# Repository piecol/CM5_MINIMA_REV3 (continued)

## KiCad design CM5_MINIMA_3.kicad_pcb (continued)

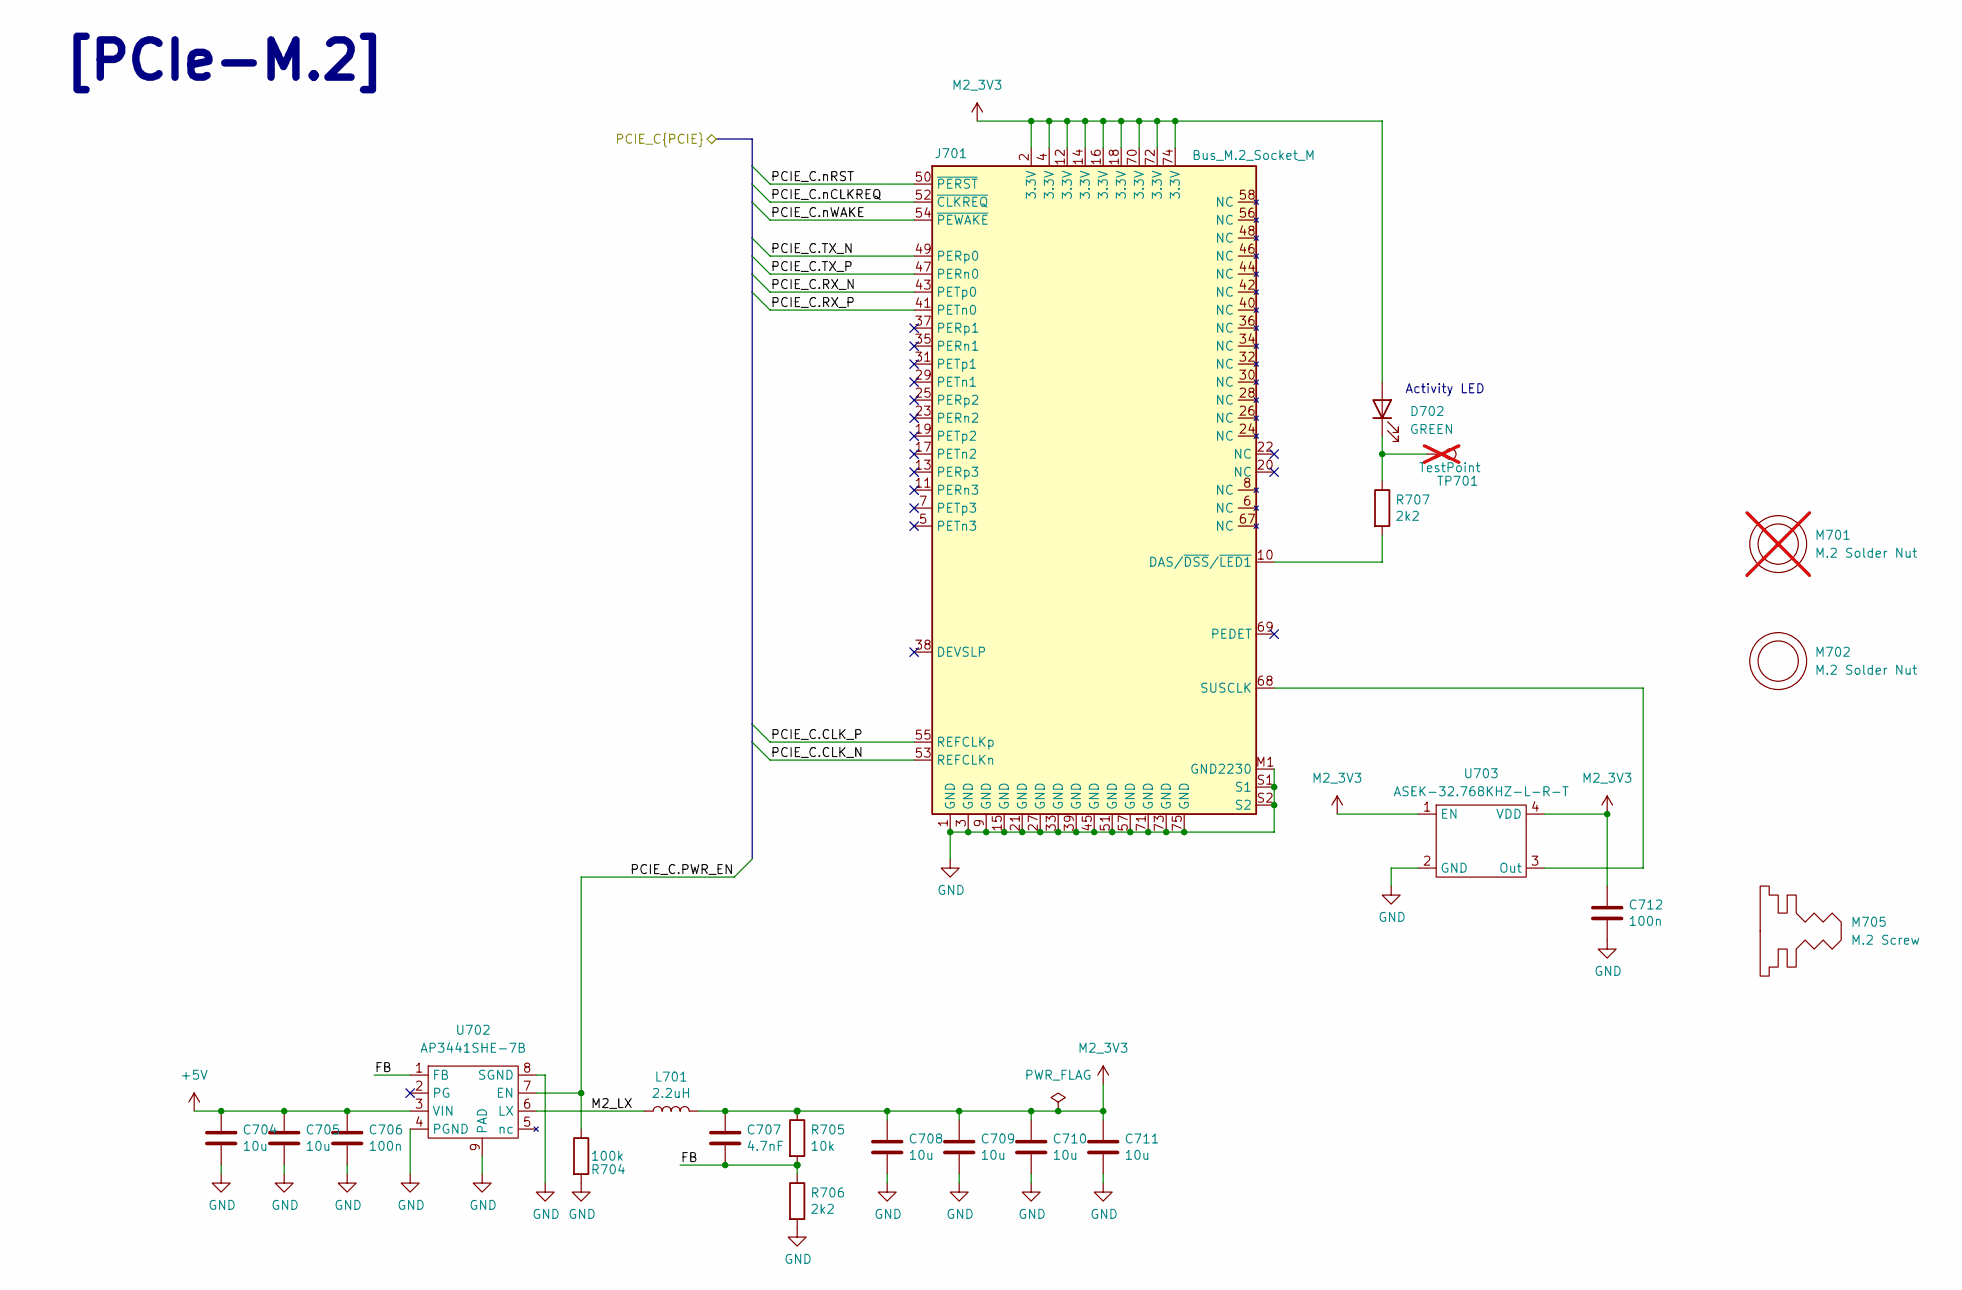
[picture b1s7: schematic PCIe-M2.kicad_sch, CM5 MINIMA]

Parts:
C704, C705, C708, C709, C710, C711: 10u; C_0805_2012Metric; Part Description 10uF 10% 10V Ceramic Capacitor X7R 0805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
C706, C712: 100n; C_0402_1005Metric; Part Description 0.1uF 10% 16V Ceramic Capacitor X7R 040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
C707: 4.7nF; C_0402_1005Metric; Part Description 4.7nF capacitor 0402
D702: GREEN; LED-SMD_L1.7-W0.6-RD
J701: Bus_M.2_Socket_M; M.2 M Key socket_2230_2242; Part Description M.2 M Key connector
L701: 2.2uH; L_Coilcraft_XAL5030-XXX; Part Description Inductor, SMT, 2u2, IRMS=7A, ISAT=8.1A,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
M701: M.2 Solder Nut; MountingHole_3mm_Pad; Part Description Solder nut for M.2 slot; not fitted
M702: M.2 Solder Nut; MountingHole_3mm_Pad; Part Description Solder nut for M.2 slot
M705: M.2 Screw; Part Description M.2 Screw
R704: 100k; R_0402_1005Metric
R705: 10k; R_0402_1005Metric
R706: 2k2; R_0402_1005Metric
R707: 2k2; R_0402_1005Metric; Part Description Resistor 1K M1005 1% 63mW
TP701: TestPoint; TestPoint_Pad_2.0x2.0mm; Part Description Test point; not fitted
U702: AP3441SHE-7B; DFN-8-1EP_2x2mm_P0.5mm_EP1.05x1.75mm; Part Description 3A DC-DC converter
U703: ASEK-32.768KHZ-L-R-T; Crystal_SMD_3225-4Pin_3.2x2.5mm; Part Description 32KHz Xtal oscilator

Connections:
+5V: C704.1, C705.1, C706.1, U702.3 (VIN); also elsewhere on the board
/CM5/PCIE_PI.CLK_N: J701.53 (REFCLKn); also elsewhere on the board
/CM5/PCIE_PI.CLK_P: J701.55 (REFCLKp); also elsewhere on the board
/CM5/PCIE_PI.PWR_EN: R704.1, U702.7 (EN); also elsewhere on the board
/CM5/PCIE_PI.RX_N: J701.43 (PETp0); also elsewhere on the board
/CM5/PCIE_PI.RX_P: J701.41 (PETn0); also elsewhere on the board
/CM5/PCIE_PI.TX_N: J701.49 (PERp0); also elsewhere on the board
/CM5/PCIE_PI.TX_P: J701.47 (PERn0); also elsewhere on the board
/CM5/PCIE_PI.nCLKREQ: J701.52 (~CLKREQ); also elsewhere on the board
/CM5/PCIE_PI.nRST: J701.50 (~PERST); also elsewhere on the board
/CM5/PCIE_PI.nWAKE: J701.54 (~PEWAKE); also elsewhere on the board
/PCIe-M2/FB: C707.2, R705.2, R706.1, U702.1 (FB)
/PCIe-M2/M2_LX: L701.1, U702.6 (LX)
GND: C704.2, C705.2, C706.2, C708.2, C709.2, C710.2, C711.2, C712.2, J701.1 (GND), J701.3 (GND), J701.9 (GND), J701.15 (GND), J701.21 (GND), J701.27 (GND), J701.33 (GND), J701.39 (GND), J701.45 (GND), J701.51 (GND), J701.57 (GND), J701.71 (GND), J701.73 (GND), J701.75 (GND), J701.M1 (GND2230), J701.S1, J701.S2, R704.2, R706.2, U702.4 (PGND), U702.8 (SGND), U702.9 (PAD), U703.2 (GND); also elsewhere on the board
M2_3V3: C707.1, C708.1, C709.1, C710.1, C711.1, C712.1, D702.2 (A), J701.2 (3.3V), J701.4 (3.3V), J701.12 (3.3V), J701.14 (3.3V), J701.16 (3.3V), J701.18 (3.3V), J701.70 (3.3V), J701.72 (3.3V), J701.74 (3.3V), L701.2, R705.1, U703.1 (EN), U703.4 (VDD)
unnamed: D702.1 (K), R707.1, TP701.1
unnamed: J701.10 (DAS/~DSS/~LED1), R707.2
unnamed: J701.68 (SUSCLK), U703.3 (Out)

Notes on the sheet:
[PCIe-M.2]
Activity LED

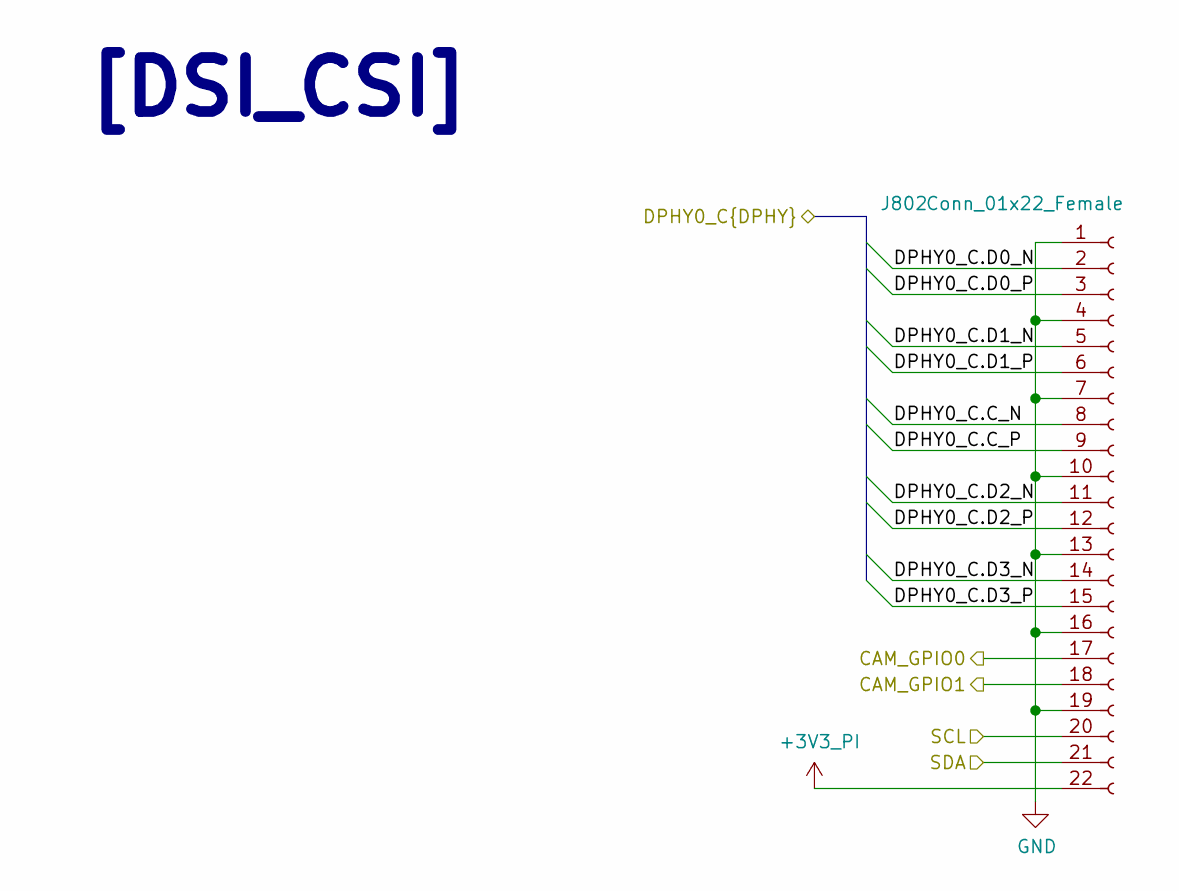
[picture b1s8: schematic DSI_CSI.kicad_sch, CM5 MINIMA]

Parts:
J802: Conn_01x22_Female; Hirose_FH12-22S-0.5SH_1x22-1MP_P0.50mm_Horizontal; Part Description 22 Position FFC, FPC Connector Contacts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

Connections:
+3V3_PI: J802.22; also elsewhere on the board
/CM5/CAM_GPIO0: J802.17; also elsewhere on the board
/CM5/CAM_GPIO1: J802.18; also elsewhere on the board
/CM5/DPHY0_P.C_N: J802.8; also elsewhere on the board
/CM5/DPHY0_P.C_P: J802.9; also elsewhere on the board
/CM5/DPHY0_P.D0_N: J802.2; also elsewhere on the board
/CM5/DPHY0_P.D0_P: J802.3; also elsewhere on the board
/CM5/DPHY0_P.D1_N: J802.5; also elsewhere on the board
/CM5/DPHY0_P.D1_P: J802.6; also elsewhere on the board
/CM5/DPHY0_P.D2_N: J802.11; also elsewhere on the board
/CM5/DPHY0_P.D2_P: J802.12; also elsewhere on the board
/CM5/DPHY0_P.D3_N: J802.14; also elsewhere on the board
/CM5/DPHY0_P.D3_P: J802.15; also elsewhere on the board
/CM5/SCL0: J802.20; also elsewhere on the board
/CM5/SDA0: J802.21; also elsewhere on the board
GND: J802.1, J802.4, J802.7, J802.10, J802.13, J802.16, J802.19; also elsewhere on the board

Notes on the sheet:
[DSI_CSI]

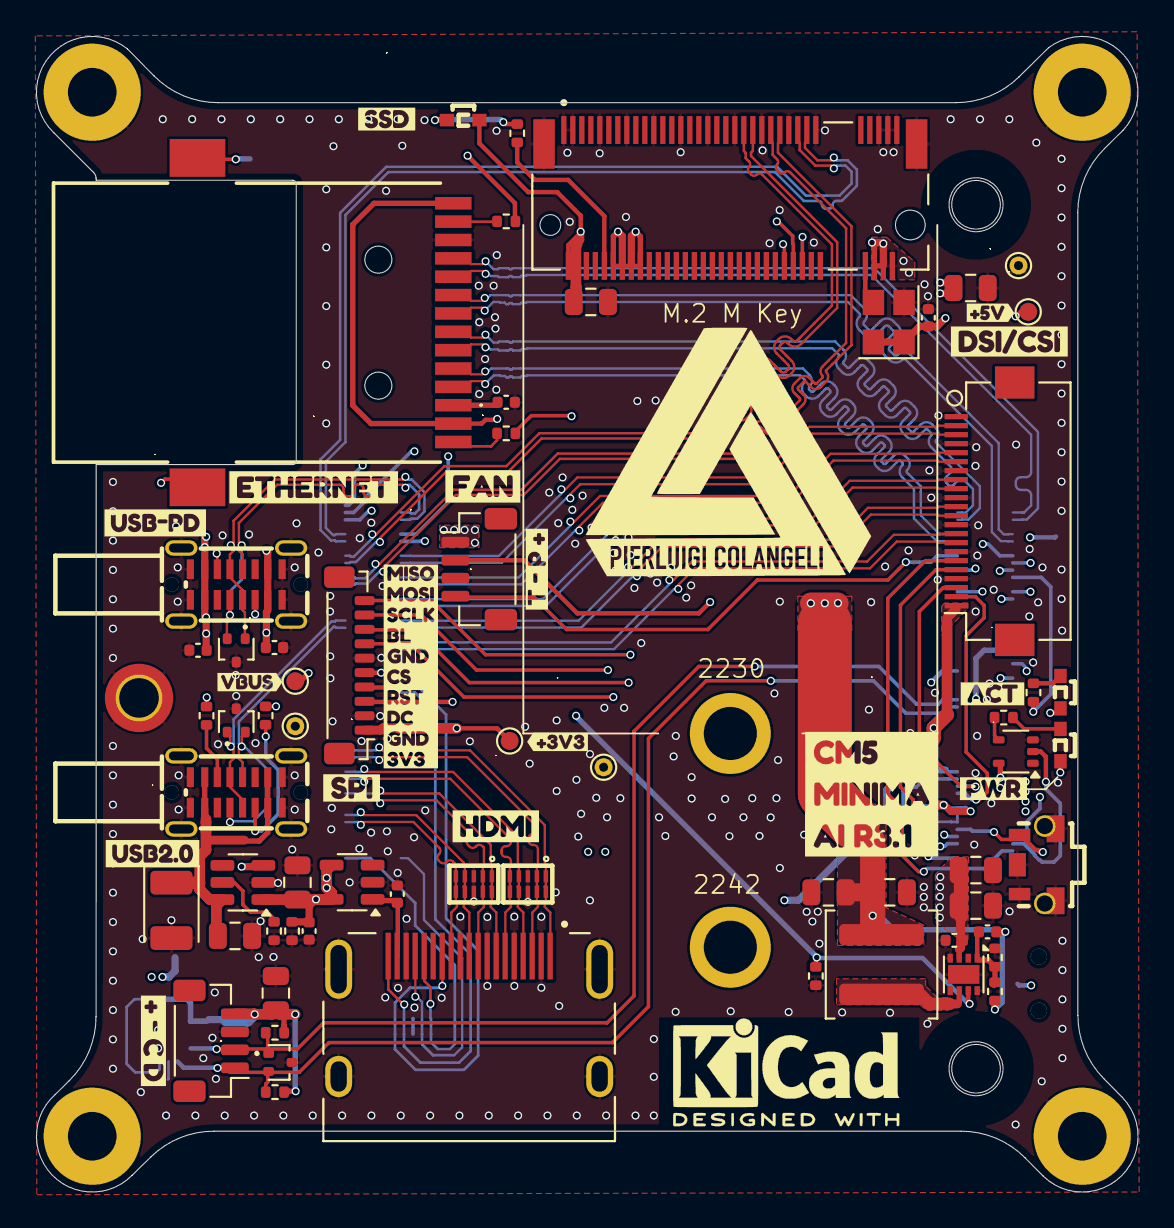
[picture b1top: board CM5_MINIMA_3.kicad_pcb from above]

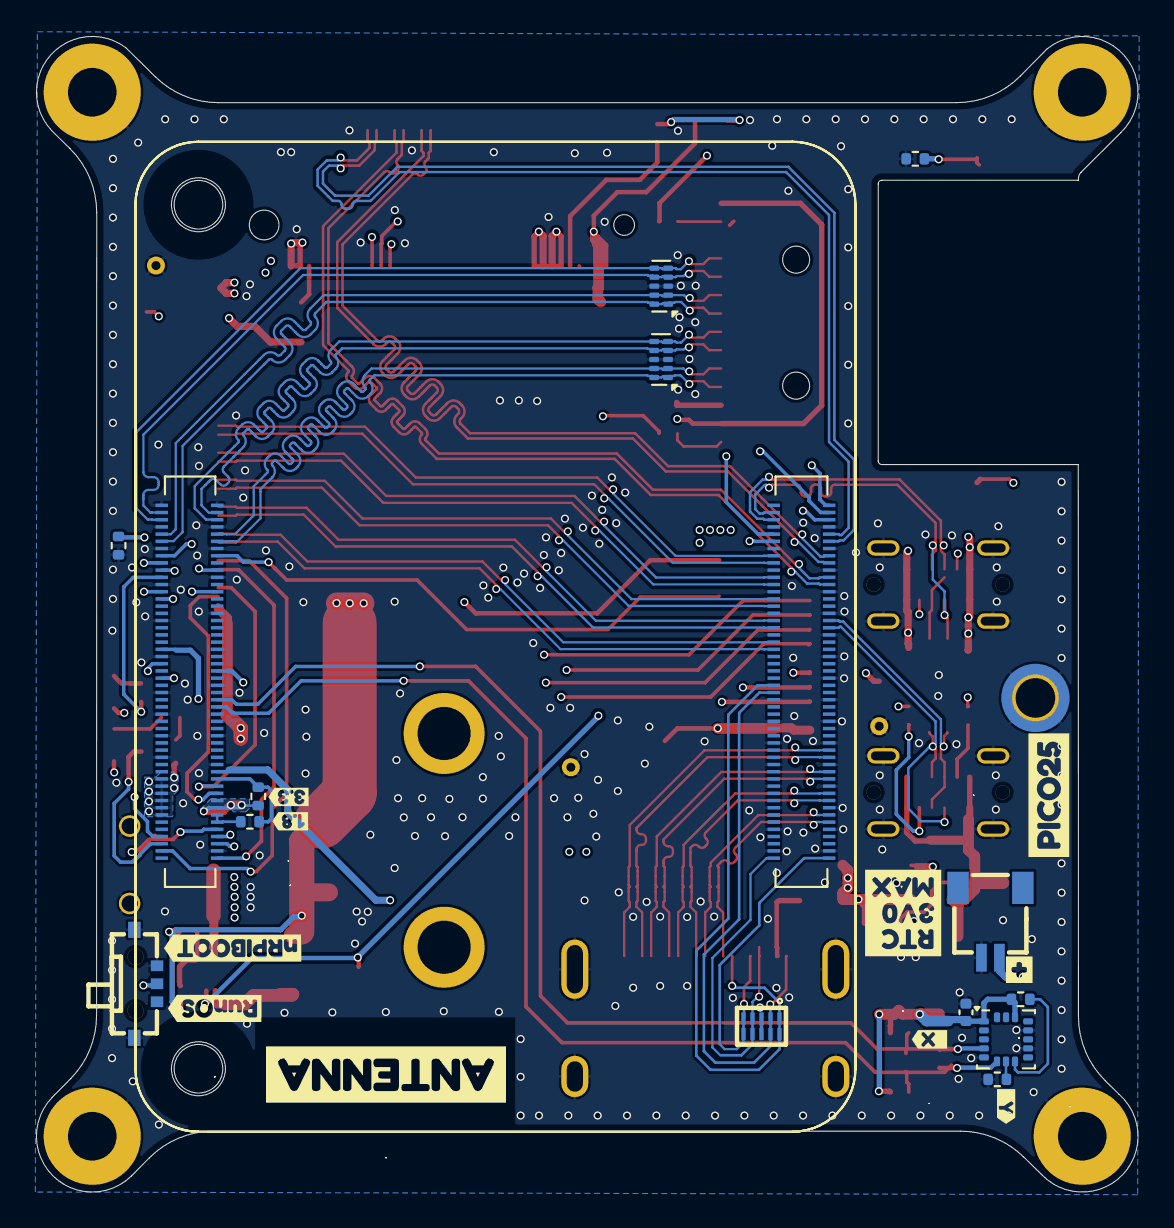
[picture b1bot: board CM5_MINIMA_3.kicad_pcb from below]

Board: 6 copper layers, 61.2 x 64.2 mm, 111 parts (25 on the bottom side), 95 nets.

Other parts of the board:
kibuzzard-67CC6BA6: G***; kibuzzard-67CC6BA6
kibuzzard-67CC6BD3: G***; kibuzzard-67CC6BD3
kibuzzard-67CC6D9E: G***; kibuzzard-67CC6D9E
kibuzzard-67CC6D94: G***; kibuzzard-67CC6D94
kibuzzard-67CC7445: G***; kibuzzard-67CC7445
kibuzzard-67EBAC4C: G***; kibuzzard-67EBAC4C
kibuzzard-67EBB9C1: G***; kibuzzard-67EBB9C1
kibuzzard-67EBD21C: G***; kibuzzard-67EBD21C
kibuzzard-67EBD221: G***; kibuzzard-67EBD221
kibuzzard-67EBEF55: G***; kibuzzard-67EBEF55
kibuzzard-67EBF0A0: G***; kibuzzard-67EBF0A0
kibuzzard-67EBF14E: G***; kibuzzard-67EBF14E
kibuzzard-67EBF015: G***; kibuzzard-67EBF015
kibuzzard-675DA838: G***; kibuzzard-675DA838
kibuzzard-675DA850: G***; kibuzzard-675DA850
kibuzzard-675DA866: G***; kibuzzard-675DA866
kibuzzard-675EDCA4: G***; kibuzzard-675EDCA4
kibuzzard-675EDCB9: G***; kibuzzard-675EDCB9
kibuzzard-6772D327: G***; kibuzzard-6772D327
kibuzzard-6772DA33: G***; kibuzzard-6772DA33
kibuzzard-6773B9CA: G***; kibuzzard-6773B9CA
kibuzzard-6773B9F7: G***; kibuzzard-6773B9F7
kibuzzard-6773BA89: G***; kibuzzard-6773BA89
kibuzzard-6773C2D7: G***; kibuzzard-6773C2D7
kibuzzard-6773C222: G***; kibuzzard-6773C222
kibuzzard-6773C376: G***; kibuzzard-6773C376
kibuzzard-67795592: G***; kibuzzard-67795592

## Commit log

2025-04-01 arcs
2025-04-01 vias
2025-04-01 DRC and prod files
2025-04-01 save exit
2025-04-02 save
2025-04-03 swapped I2C bus from 0 to 1
2025-04-03 drc ok
2025-04-08 eth PCB new
2025-04-10 exit
2025-06-12 SEEED
2025-06-25 assembly plot
2025-06-25 readme
2025-06-25 licence
2025-08-29 NEXTPCB production files
2025-09-30 case added
2025-12-03 ave from terminal
2026-01-22 STEP upload
